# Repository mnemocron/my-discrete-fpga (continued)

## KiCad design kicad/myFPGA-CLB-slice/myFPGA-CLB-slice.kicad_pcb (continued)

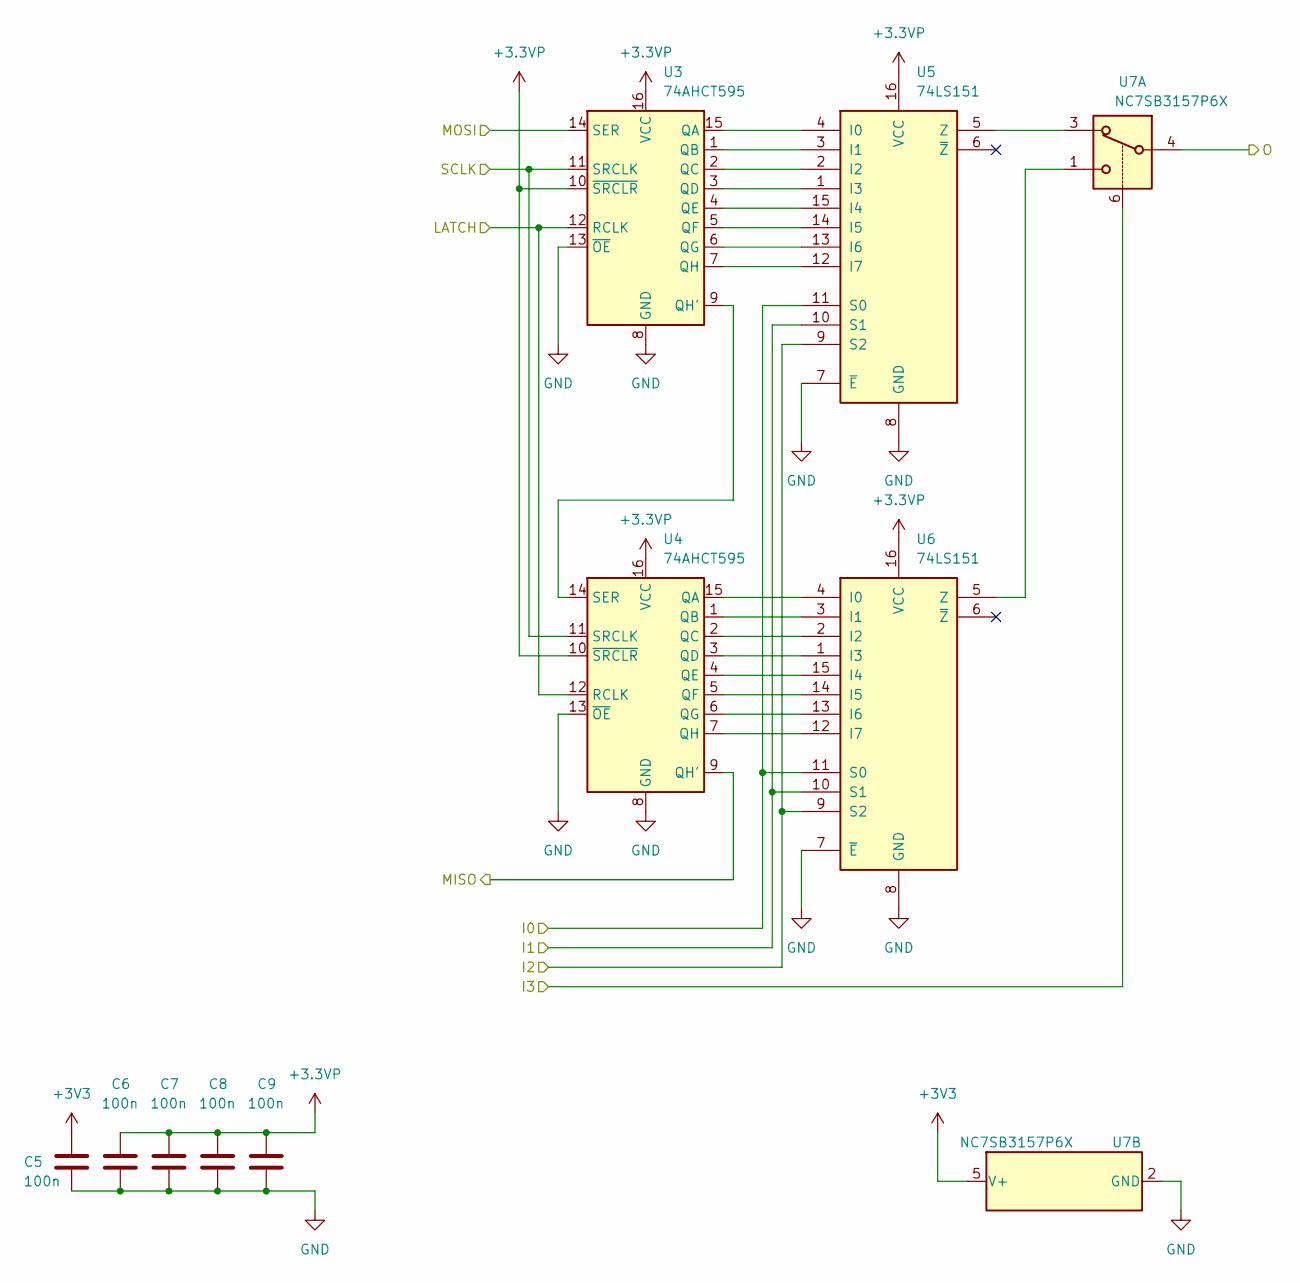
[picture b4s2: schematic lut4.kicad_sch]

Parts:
C5, C6, C7, C8, C9: 100n; C_0603_1608Metric; Voltage 50; Part Nr. CC0603KRX7R9BB104; JLCPCB Part # C14663
U3, U4: 74AHCT595; SOIC-16_3.9x9.9mm_P1.27mm; Part Nr. 74HC595D; JLCPCB Part # C5947
U5, U6: 74LS151; TSSOP-16_4.4x5mm_P0.65mm; Part Nr. MC74HC151ADTR2G; JLCPCB Part # C152523
U7: NC7SB3157P6X; SOT-363_SC-70-6; Part Nr. 74LVC1G157GW; JLCPCB Part # C135822

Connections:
+3.3VP: C6.1, C7.1, C8.1, C9.1, U3.10 (~SRCLR), U3.16 (VCC), U4.10 (~SRCLR), U4.16 (VCC), U5.16 (VCC), U6.16 (VCC); also elsewhere on the board
+3V3: C5.1, U7.5 (V+); also elsewhere on the board
/CBpre_2: U5.9 (S2), U6.9 (S2); also elsewhere on the board
/CBpre_3: U7.6; also elsewhere on the board
/D0: U5.10 (S1), U6.10 (S1); also elsewhere on the board
/D1: U5.11 (S0), U6.11 (S0); also elsewhere on the board
/Input Selector/MISO: U3.14 (SER); also elsewhere on the board
/LUT4_0/MISO: U4.9 (QH'); also elsewhere on the board
/Ld: U7.4; also elsewhere on the board
GND: C5.2, C6.2, C7.2, C8.2, C9.2, U3.8 (GND), U3.13 (~OE), U4.8 (GND), U4.13 (~OE), U5.7 (~E), U5.8 (GND), U6.7 (~E), U6.8 (GND), U7.2 (GND); also elsewhere on the board
LATCH: U3.12 (RCLK), U4.12 (RCLK); also elsewhere on the board
unnamed: U3.15 (QA), U5.4 (I0)
unnamed: U3.1 (QB), U5.3 (I1)
unnamed: U3.2 (QC), U5.2 (I2)
unnamed: U3.3 (QD), U5.1 (I3)
unnamed: U3.4 (QE), U5.15 (I4)
unnamed: U3.5 (QF), U5.14 (I5)
unnamed: U3.6 (QG), U5.13 (I6)
unnamed: U3.9 (QH'), U4.14 (SER)
unnamed: U3.7 (QH), U5.12 (I7)
unnamed: U4.15 (QA), U6.4 (I0)
unnamed: U4.1 (QB), U6.3 (I1)
unnamed: U4.2 (QC), U6.2 (I2)
unnamed: U4.3 (QD), U6.1 (I3)
unnamed: U4.4 (QE), U6.15 (I4)
unnamed: U4.5 (QF), U6.14 (I5)
unnamed: U4.6 (QG), U6.13 (I6)
unnamed: U4.7 (QH), U6.12 (I7)
unnamed: U5.5 (Z), U7.3
unnamed: U6.5 (Z), U7.1
SCLK: U3.11 (SRCLK), U4.11 (SRCLK); also elsewhere on the board

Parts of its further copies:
C20, C21, C22, C23, C24, C25, C26, C27, C28, C29, C30, C31, C32, C33, C34: 100n; C_0603_1608Metric; Voltage 50; Part Nr. CC0603KRX7R9BB104; JLCPCB Part # C14663
U19, U20, U24, U25, U29, U30: 74AHCT595; SOIC-16_3.9x9.9mm_P1.27mm; Part Nr. 74HC595D; JLCPCB Part # C5947
U21, U22, U26, U27, U31, U32: 74LS151; TSSOP-16_4.4x5mm_P0.65mm; Part Nr. MC74HC151ADTR2G; JLCPCB Part # C152523
U23, U28, U33: NC7SB3157P6X; SOT-363_SC-70-6; Part Nr. 74LVC1G157GW; JLCPCB Part # C135822

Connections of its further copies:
+3.3VP: C21.1, C22.1, C23.1, C24.1, C26.1, C27.1, C28.1, C29.1, C31.1, C32.1, C33.1, C34.1, U19.10 (~SRCLR), U19.16 (VCC), U20.10 (~SRCLR), U20.16 (VCC), U21.16 (VCC), U22.16 (VCC), U24.10 (~SRCLR), U24.16 (VCC), U25.10 (~SRCLR), U25.16 (VCC), U26.16 (VCC), U27.16 (VCC), U29.10 (~SRCLR), U29.16 (VCC), U30.10 (~SRCLR), U30.16 (VCC), U31.16 (VCC), U32.16 (VCC); also elsewhere on the board
+3V3: C20.1, C25.1, C30.1, U23.5 (V+), U28.5 (V+), U33.5 (V+); also elsewhere on the board
/A0: U31.10 (S1), U32.10 (S1); also elsewhere on the board
/A1: U31.11 (S0), U32.11 (S0); also elsewhere on the board
/B0: U26.10 (S1), U27.10 (S1); also elsewhere on the board
/B1: U26.11 (S0), U27.11 (S0); also elsewhere on the board
/C0: U21.10 (S1), U22.10 (S1); also elsewhere on the board
/C1: U21.11 (S0), U22.11 (S0); also elsewhere on the board
/CBpre_2: U21.9 (S2), U22.9 (S2), U26.9 (S2), U27.9 (S2), U31.9 (S2), U32.9 (S2); also elsewhere on the board
/CBpre_3: U23.6, U28.6, U33.6; also elsewhere on the board
/LUT4_0/MISO: U19.14 (SER); also elsewhere on the board
/LUT4_1/MISO: U20.9 (QH'), U24.14 (SER)
/LUT4_2/MISO: U25.9 (QH'), U29.14 (SER)
/LUT4_3/MISO: U30.9 (QH'); also elsewhere on the board
/La: U33.4; also elsewhere on the board
/Lb: U28.4; also elsewhere on the board
/Lc: U23.4; also elsewhere on the board
GND: C20.2, C21.2, C22.2, C23.2, C24.2, C25.2, C26.2, C27.2, C28.2, C29.2, C30.2, C31.2, C32.2, C33.2, C34.2, U19.8 (GND), U19.13 (~OE), U20.8 (GND), U20.13 (~OE), U21.7 (~E), U21.8 (GND), U22.7 (~E), U22.8 (GND), U23.2 (GND), U24.8 (GND), U24.13 (~OE), U25.8 (GND), U25.13 (~OE), U26.7 (~E), U26.8 (GND), U27.7 (~E), U27.8 (GND), U28.2 (GND), U29.8 (GND), U29.13 (~OE), U30.8 (GND), U30.13 (~OE), U31.7 (~E), U31.8 (GND), U32.7 (~E), U32.8 (GND), U33.2 (GND); also elsewhere on the board
LATCH: U19.12 (RCLK), U20.12 (RCLK), U24.12 (RCLK), U25.12 (RCLK), U29.12 (RCLK), U30.12 (RCLK); also elsewhere on the board
unnamed: U19.15 (QA), U21.4 (I0)
unnamed: U19.1 (QB), U21.3 (I1)
unnamed: U19.2 (QC), U21.2 (I2)
unnamed: U19.3 (QD), U21.1 (I3)
unnamed: U19.4 (QE), U21.15 (I4)
unnamed: U19.5 (QF), U21.14 (I5)
unnamed: U19.6 (QG), U21.13 (I6)
unnamed: U19.9 (QH'), U20.14 (SER)
unnamed: U19.7 (QH), U21.12 (I7)
unnamed: U20.15 (QA), U22.4 (I0)
unnamed: U20.1 (QB), U22.3 (I1)
unnamed: U20.2 (QC), U22.2 (I2)
unnamed: U20.3 (QD), U22.1 (I3)
unnamed: U20.4 (QE), U22.15 (I4)
unnamed: U20.5 (QF), U22.14 (I5)
unnamed: U20.6 (QG), U22.13 (I6)
unnamed: U20.7 (QH), U22.12 (I7)
unnamed: U21.5 (Z), U23.3
unnamed: U22.5 (Z), U23.1
unnamed: U24.15 (QA), U26.4 (I0)
unnamed: U24.1 (QB), U26.3 (I1)
unnamed: U24.2 (QC), U26.2 (I2)
unnamed: U24.3 (QD), U26.1 (I3)
unnamed: U24.4 (QE), U26.15 (I4)
unnamed: U24.5 (QF), U26.14 (I5)
unnamed: U24.6 (QG), U26.13 (I6)
unnamed: U24.9 (QH'), U25.14 (SER)
unnamed: U24.7 (QH), U26.12 (I7)
unnamed: U25.15 (QA), U27.4 (I0)
unnamed: U25.1 (QB), U27.3 (I1)
unnamed: U25.2 (QC), U27.2 (I2)
unnamed: U25.3 (QD), U27.1 (I3)
unnamed: U25.4 (QE), U27.15 (I4)
unnamed: U25.5 (QF), U27.14 (I5)
unnamed: U25.6 (QG), U27.13 (I6)
unnamed: U25.7 (QH), U27.12 (I7)
unnamed: U26.5 (Z), U28.3
unnamed: U27.5 (Z), U28.1
unnamed: U29.15 (QA), U31.4 (I0)
unnamed: U29.1 (QB), U31.3 (I1)
unnamed: U29.2 (QC), U31.2 (I2)
unnamed: U29.3 (QD), U31.1 (I3)
unnamed: U29.4 (QE), U31.15 (I4)
unnamed: U29.5 (QF), U31.14 (I5)
unnamed: U29.6 (QG), U31.13 (I6)
unnamed: U29.9 (QH'), U30.14 (SER)
unnamed: U29.7 (QH), U31.12 (I7)
unnamed: U30.15 (QA), U32.4 (I0)
unnamed: U30.1 (QB), U32.3 (I1)
unnamed: U30.2 (QC), U32.2 (I2)
unnamed: U30.3 (QD), U32.1 (I3)
unnamed: U30.4 (QE), U32.15 (I4)
unnamed: U30.5 (QF), U32.14 (I5)
unnamed: U30.6 (QG), U32.13 (I6)
unnamed: U30.7 (QH), U32.12 (I7)
unnamed: U31.5 (Z), U33.3
unnamed: U32.5 (Z), U33.1
SCLK: U19.11 (SRCLK), U20.11 (SRCLK), U24.11 (SRCLK), U25.11 (SRCLK), U29.11 (SRCLK), U30.11 (SRCLK); also elsewhere on the board

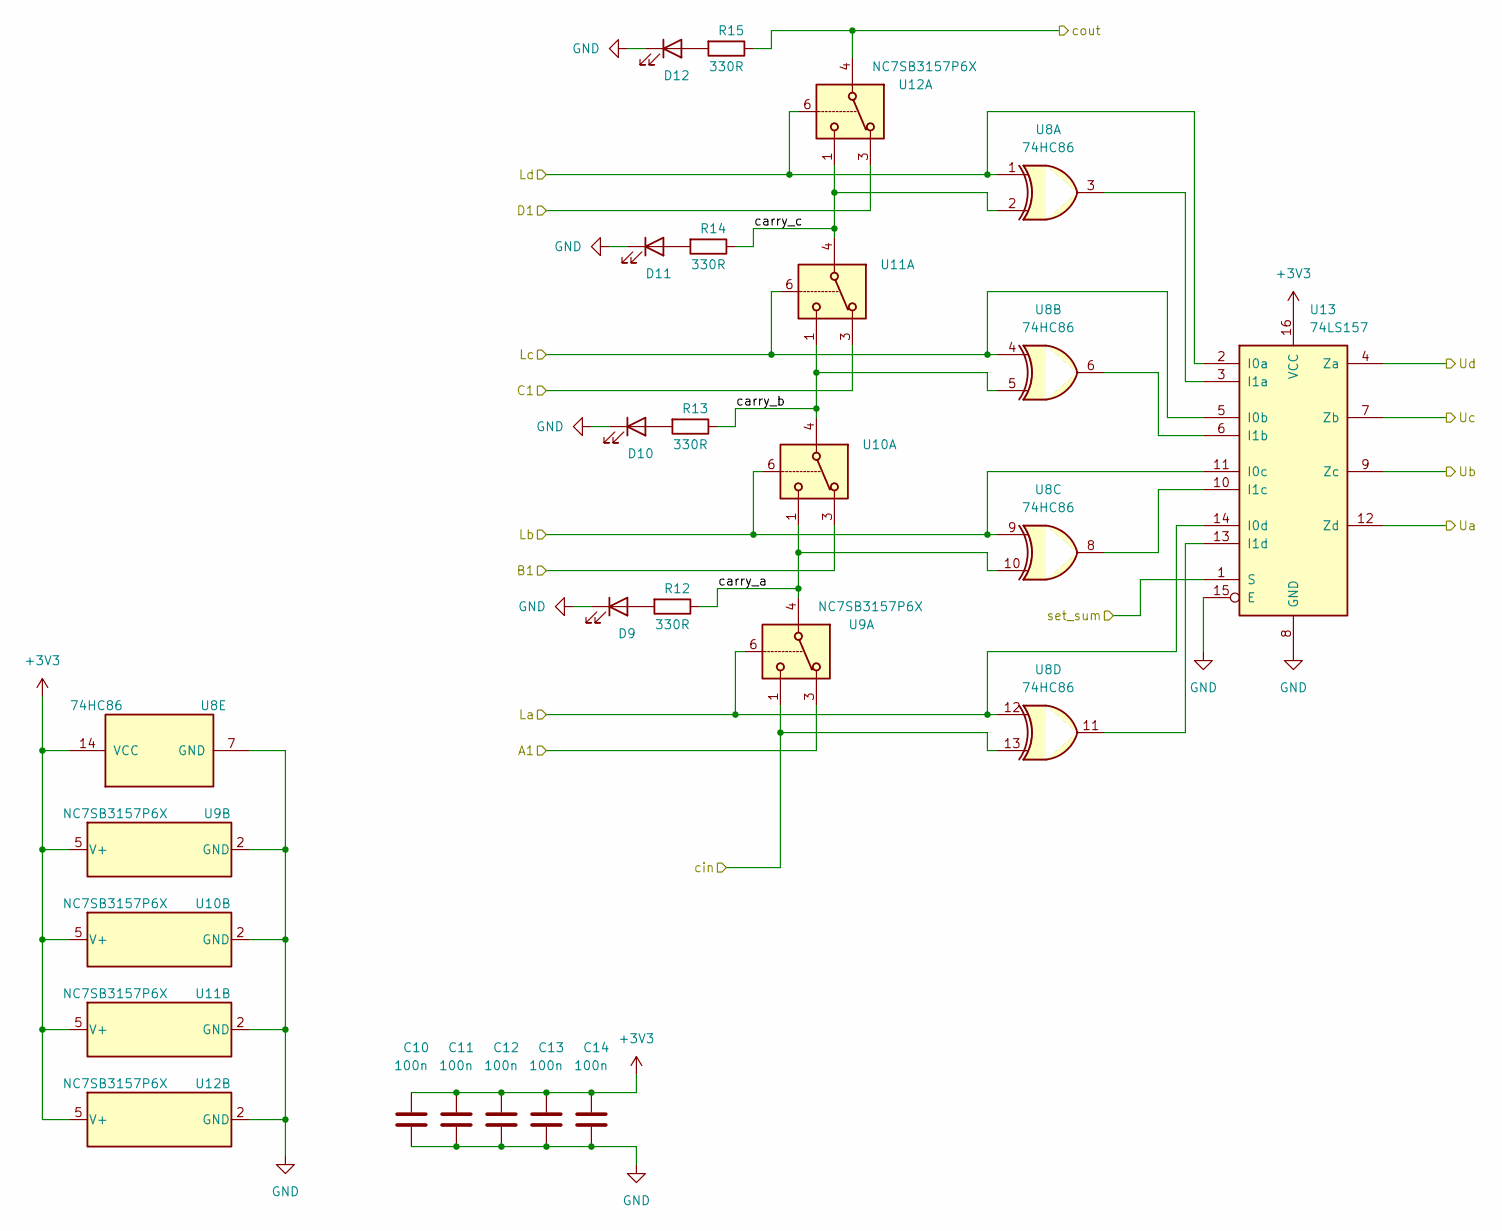
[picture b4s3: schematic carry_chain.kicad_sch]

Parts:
C10, C11, C12, C13, C14: 100n; C_0603_1608Metric; Voltage 50; Part Nr. CC0603KRX7R9BB104; JLCPCB Part # C14663
D9, D10, D11, D12: LED (blue); LED_0603_1608Metric; Part Nr. 19-217/BHC-ZL1M2RY/3T; JLCPCB Part # C72041
R12, R13, R14, R15: 330R; R_0603_1608Metric; Part Nr. 0603WAF3300T5E; JLCPCB Part # C23138
U8: 74HC86; SOIC-14_3.9x8.7mm_P1.27mm; Part Nr. SN74AHC86DR; JLCPCB Part # C8175
U9, U10, U11, U12: NC7SB3157P6X; SOT-363_SC-70-6; Part Nr. 74LVC1G157GW; JLCPCB Part # C135822
U13: 74LS157; SOIC-16_3.9x9.9mm_P1.27mm; Part Nr. SN74HC157DR; JLCPCB Part # C6823

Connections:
+3V3: C10.1, C11.1, C12.1, C13.1, C14.1, U8.14 (VCC), U9.5 (V+), U10.5 (V+), U11.5 (V+), U12.5 (V+), U13.16 (VCC); also elsewhere on the board
/A0: U9.3; also elsewhere on the board
/B0: U10.3; also elsewhere on the board
/C0: U11.3; also elsewhere on the board
/Carry Chain/carry_a: R12.1, U8.10, U9.4, U10.1
/Carry Chain/carry_b: R13.1, U8.5, U10.4, U11.1
/Carry Chain/carry_c: R14.1, U8.2, U11.4, U12.1
/D0: U12.3; also elsewhere on the board
/La: U8.12, U9.6, U13.14 (I0d); also elsewhere on the board
/Lb: U8.9, U10.6, U13.11 (I0c); also elsewhere on the board
/Lc: U8.4, U11.6, U13.5 (I0b); also elsewhere on the board
/Ld: U8.1, U12.6, U13.2 (I0a); also elsewhere on the board
/Oa: U13.12 (Zd); also elsewhere on the board
/Ob: U13.9 (Zc); also elsewhere on the board
/Oc: U13.7 (Zb); also elsewhere on the board
/Od: U13.4 (Za); also elsewhere on the board
/cin: U8.13, U9.1; also elsewhere on the board
/cout: R15.1, U12.4; also elsewhere on the board
GND: C10.2, C11.2, C12.2, C13.2, C14.2, D9.1 (K), D10.1 (K), D11.1 (K), D12.1 (K), U8.7 (GND), U9.2 (GND), U10.2 (GND), U11.2 (GND), U12.2 (GND), U13.8 (GND), U13.15 (E); also elsewhere on the board
unnamed: D9.2 (A), R12.2
unnamed: D10.2 (A), R13.2
unnamed: D11.2 (A), R14.2
unnamed: D12.2 (A), R15.2
unnamed: U8.3, U13.3 (I1a)
unnamed: U8.6, U13.6 (I1b)
unnamed: U8.8, U13.10 (I1c)
unnamed: U8.11, U13.13 (I1d)
set_sum: U13.1 (S); also elsewhere on the board

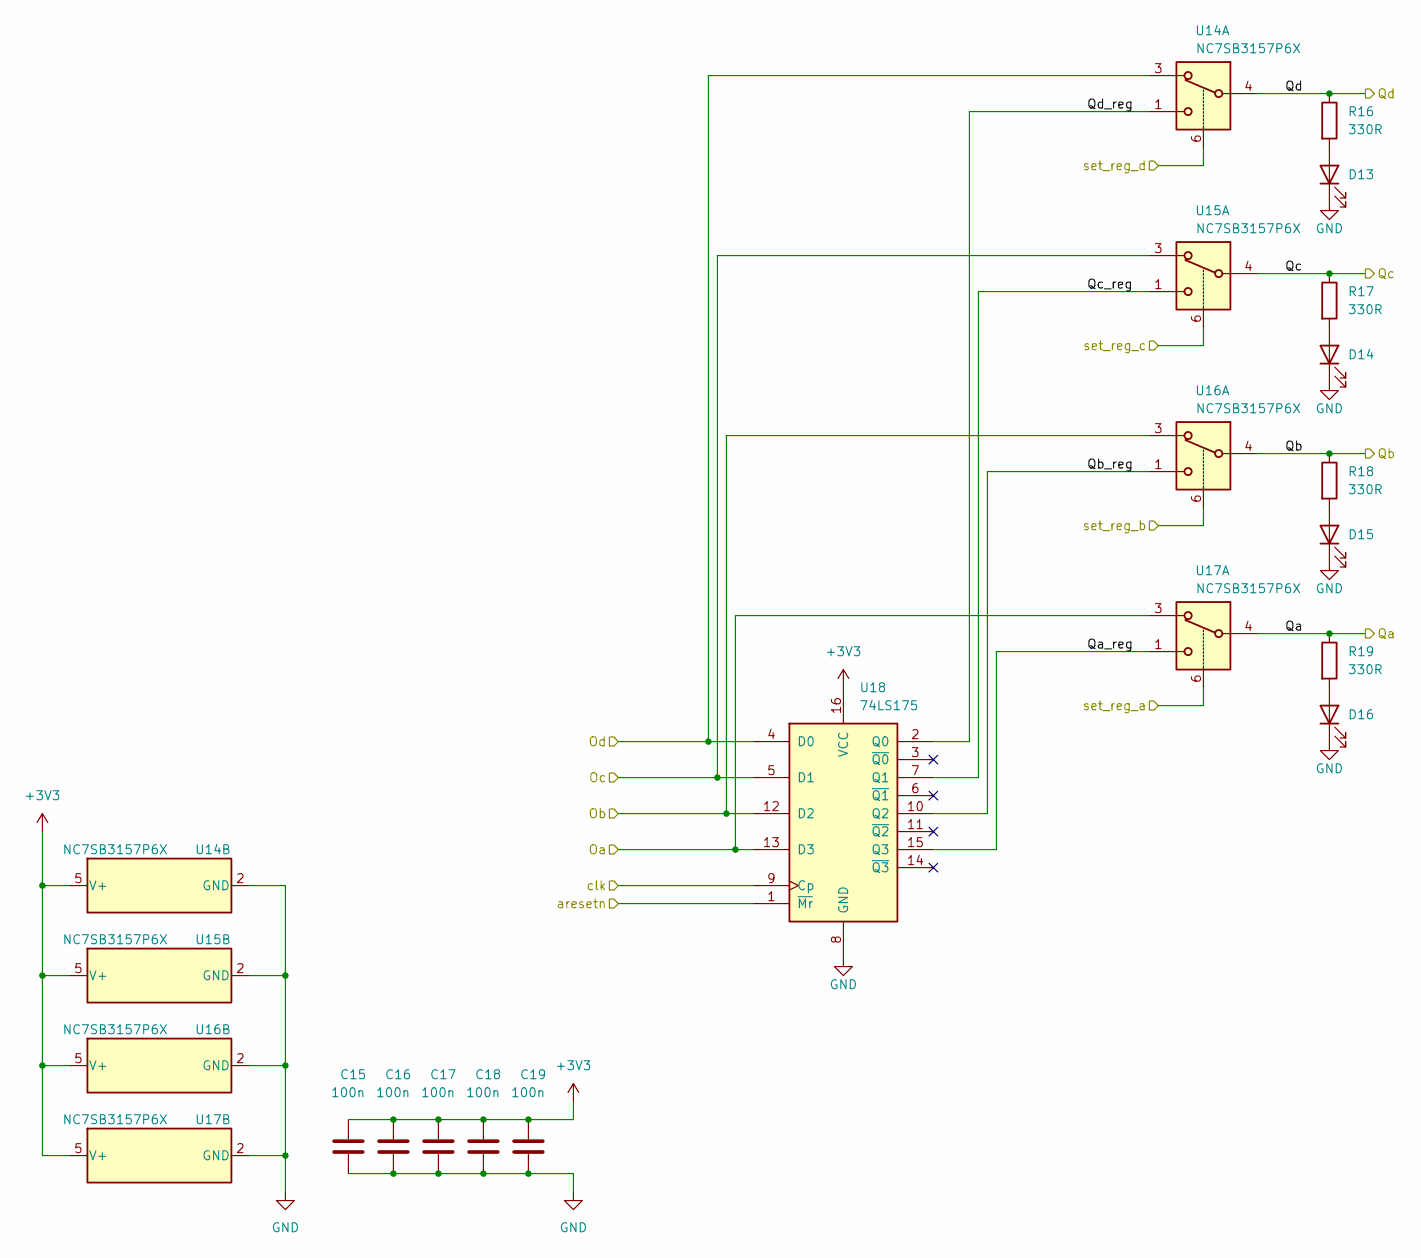
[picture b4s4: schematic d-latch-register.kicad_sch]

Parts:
C15, C16, C17, C18, C19: 100n; C_0603_1608Metric; Voltage 50; Part Nr. CC0603KRX7R9BB104; JLCPCB Part # C14663
D13, D14, D15, D16: LED (blue); LED_0603_1608Metric; Part Nr. 19-217/BHC-ZL1M2RY/3T; JLCPCB Part # C72041
R16, R17, R18, R19: 330R; R_0603_1608Metric; Part Nr. 0603WAF3300T5E; JLCPCB Part # C23138
U14, U15, U16, U17: NC7SB3157P6X; SOT-363_SC-70-6; Part Nr. 74LVC1G157GW; JLCPCB Part # C135822
U18: 74LS175; SOIC-16_3.9x9.9mm_P1.27mm; Part Nr. CD74AC175M96; JLCPCB Part # C8180

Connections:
+3V3: C15.1, C16.1, C17.1, C18.1, C19.1, U14.5 (V+), U15.5 (V+), U16.5 (V+), U17.5 (V+), U18.16 (VCC); also elsewhere on the board
/D-Latch/Qa: R19.1, U17.4; also elsewhere on the board
/D-Latch/Qa_reg: U17.1, U18.15 (Q3)
/D-Latch/Qb: R18.1, U16.4; also elsewhere on the board
/D-Latch/Qb_reg: U16.1, U18.10 (Q2)
/D-Latch/Qc: R17.1, U15.4; also elsewhere on the board
/D-Latch/Qc_reg: U15.1, U18.7 (Q1)
/D-Latch/Qd: R16.1, U14.4; also elsewhere on the board
/D-Latch/Qd_reg: U14.1, U18.2 (Q0)
/Oa: U17.3, U18.13 (D3); also elsewhere on the board
/Ob: U16.3, U18.12 (D2); also elsewhere on the board
/Oc: U15.3, U18.5 (D1); also elsewhere on the board
/Od: U14.3, U18.4 (D0); also elsewhere on the board
GND: C15.2, C16.2, C17.2, C18.2, C19.2, D13.1 (K), D14.1 (K), D15.1 (K), D16.1 (K), U14.2 (GND), U15.2 (GND), U16.2 (GND), U17.2 (GND), U18.8 (GND); also elsewhere on the board
unnamed: D13.2 (A), R16.2
unnamed: D14.2 (A), R17.2
unnamed: D15.2 (A), R18.2
unnamed: D16.2 (A), R19.2
aresetn: U18.1 (~Mr); also elsewhere on the board
latch_clk: U18.9 (Cp); also elsewhere on the board
set_reg_a: U17.6; also elsewhere on the board
set_reg_b: U16.6; also elsewhere on the board
set_reg_c: U15.6; also elsewhere on the board
set_reg_d: U14.6; also elsewhere on the board

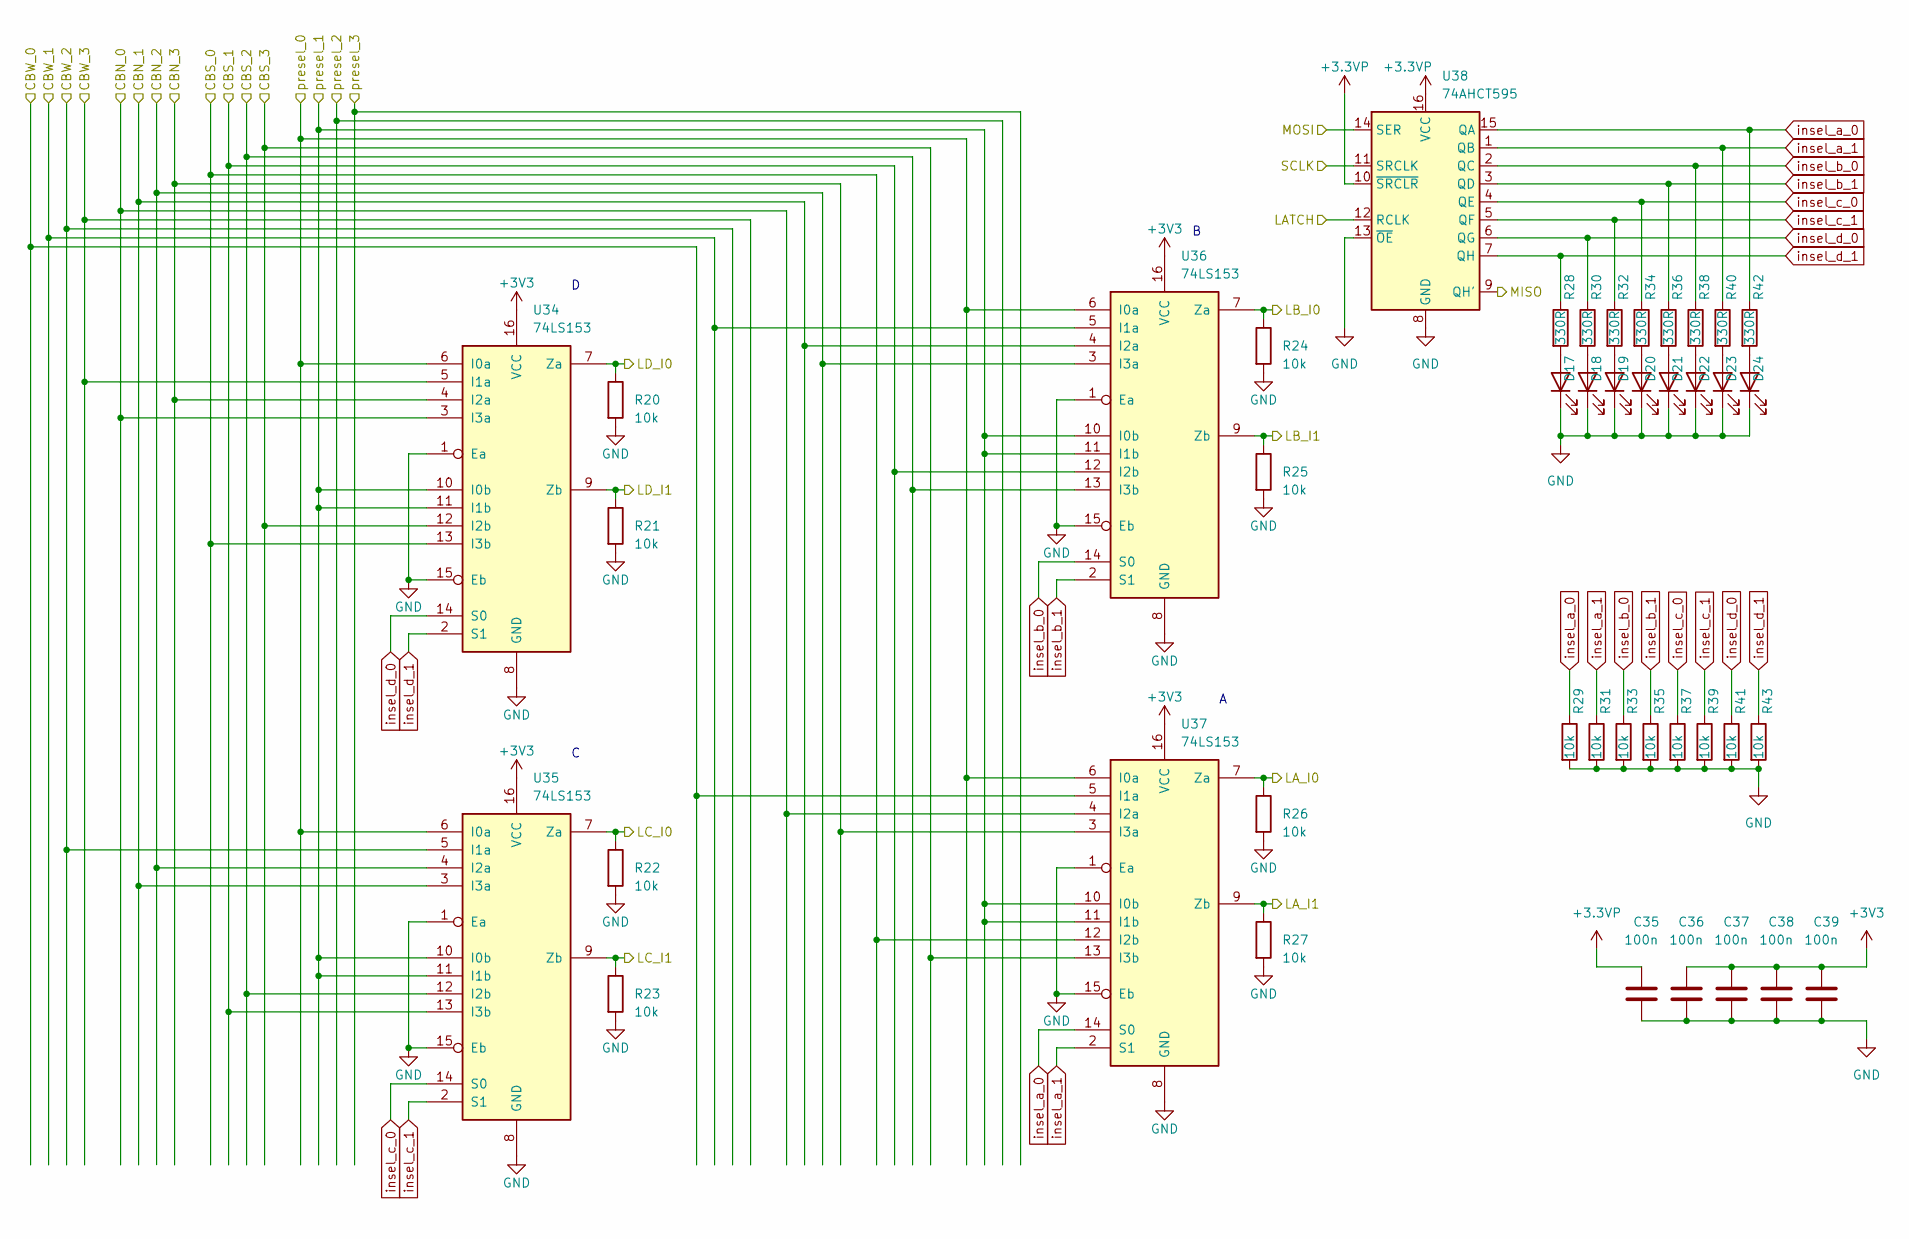
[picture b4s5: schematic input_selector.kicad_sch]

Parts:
C35, C36, C37, C38, C39: 100n; C_0603_1608Metric; Voltage 50; Part Nr. CC0603KRX7R9BB104; JLCPCB Part # C14663
D17, D18, D19, D20, D21, D22, D23, D24: LED (green); LED_0805_2012Metric; Part Nr. C2297; JLCPCB Part # C2297
R20, R21, R22, R23, R24, R25, R26, R27, R29, R31, R33, R35, R37, R39, R41, R43: 10k; R_0603_1608Metric; Part Nr. 0603WAF1002T5E; JLCPCB Part # C25804
R28, R30, R32, R34, R36, R38, R40, R42: 330R; R_0603_1608Metric; Part Nr. 0603WAF3300T5E; JLCPCB Part # C23138
U34, U35, U36, U37: 74LS153; TSSOP-16_4.4x5mm_P0.65mm; Part Nr. 74HC153D; JLCPCB Part # C150159
U38: 74AHCT595; SOIC-16_3.9x9.9mm_P1.27mm; Part Nr. 74HC595D; JLCPCB Part # C5947

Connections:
+3.3VP: C35.1, U38.10 (~SRCLR), U38.16 (VCC); also elsewhere on the board
+3V3: C36.1, C37.1, C38.1, C39.1, U34.16 (VCC), U35.16 (VCC), U36.16 (VCC), U37.16 (VCC); also elsewhere on the board
/A0: R26.1, U37.7 (Za); also elsewhere on the board
/A1: R27.1, U37.9 (Zb); also elsewhere on the board
/B0: R24.1, U36.7 (Za); also elsewhere on the board
/B1: R25.1, U36.9 (Zb); also elsewhere on the board
/C0: R22.1, U35.7 (Za); also elsewhere on the board
/C1: R23.1, U35.9 (Zb); also elsewhere on the board
/CBpre_0: U34.6 (I0a), U35.6 (I0a), U36.6 (I0a), U37.6 (I0a); also elsewhere on the board
/CBpre_1: U34.10 (I0b), U34.11 (I1b), U35.10 (I0b), U35.11 (I1b), U36.10 (I0b), U36.11 (I1b), U37.10 (I0b), U37.11 (I1b); also elsewhere on the board
/CBw_0: U37.5 (I1a); also elsewhere on the board
/CBw_1: U36.5 (I1a); also elsewhere on the board
/CBw_2: U35.5 (I1a); also elsewhere on the board
/CBw_3: U34.5 (I1a); also elsewhere on the board
/D0: R20.1, U34.7 (Za); also elsewhere on the board
/D1: R21.1, U34.9 (Zb); also elsewhere on the board
/Input Selector/CBN_0: U34.3 (I3a), U37.4 (I2a); also elsewhere on the board
/Input Selector/CBN_1: U35.3 (I3a), U36.4 (I2a); also elsewhere on the board
/Input Selector/CBN_2: U35.4 (I2a), U36.3 (I3a); also elsewhere on the board
/Input Selector/CBN_3: U34.4 (I2a), U37.3 (I3a); also elsewhere on the board
/Input Selector/CBS_0: U34.13 (I3b), U37.12 (I2b); also elsewhere on the board
/Input Selector/CBS_1: U35.13 (I3b), U36.12 (I2b); also elsewhere on the board
/Input Selector/CBS_2: U35.12 (I2b), U36.13 (I3b); also elsewhere on the board
/Input Selector/CBS_3: U34.12 (I2b), U37.13 (I3b); also elsewhere on the board
/Input Selector/MISO: U38.9 (QH'); also elsewhere on the board
GND: C35.2, C36.2, C37.2, C38.2, C39.2, D17.1 (K), D18.1 (K), D19.1 (K), D20.1 (K), D21.1 (K), D22.1 (K), D23.1 (K), D24.1 (K), R20.2, R21.2, R22.2, R23.2, R24.2, R25.2, R26.2, R27.2, R29.2, R31.2, R33.2, R35.2, R37.2, R39.2, R41.2, R43.2, U34.1 (Ea), U34.8 (GND), U34.15 (Eb), U35.1 (Ea), U35.8 (GND), U35.15 (Eb), U36.1 (Ea), U36.8 (GND), U36.15 (Eb), U37.1 (Ea), U37.8 (GND), U37.15 (Eb), U38.8 (GND), U38.13 (~OE); also elsewhere on the board
LATCH: U38.12 (RCLK); also elsewhere on the board
MOSI: U38.14 (SER); also elsewhere on the board
unnamed: D17.2 (A), R28.2
unnamed: D18.2 (A), R30.2
unnamed: D19.2 (A), R32.2
unnamed: D20.2 (A), R34.2
unnamed: D21.2 (A), R36.2
unnamed: D22.2 (A), R38.2
unnamed: D23.2 (A), R40.2
unnamed: D24.2 (A), R42.2
SCLK: U38.11 (SRCLK); also elsewhere on the board
insel_a_0: R29.1, R42.1, U37.14 (S0), U38.15 (QA)
insel_a_1: R31.1, R40.1, U37.2 (S1), U38.1 (QB)
insel_b_0: R33.1, R38.1, U36.14 (S0), U38.2 (QC)
insel_b_1: R35.1, R36.1, U36.2 (S1), U38.3 (QD)
insel_c_0: R34.1, R37.1, U35.14 (S0), U38.4 (QE)
insel_c_1: R32.1, R39.1, U35.2 (S1), U38.5 (QF)
insel_d_0: R30.1, R41.1, U34.14 (S0), U38.6 (QG)
insel_d_1: R28.1, R43.1, U34.2 (S1), U38.7 (QH)

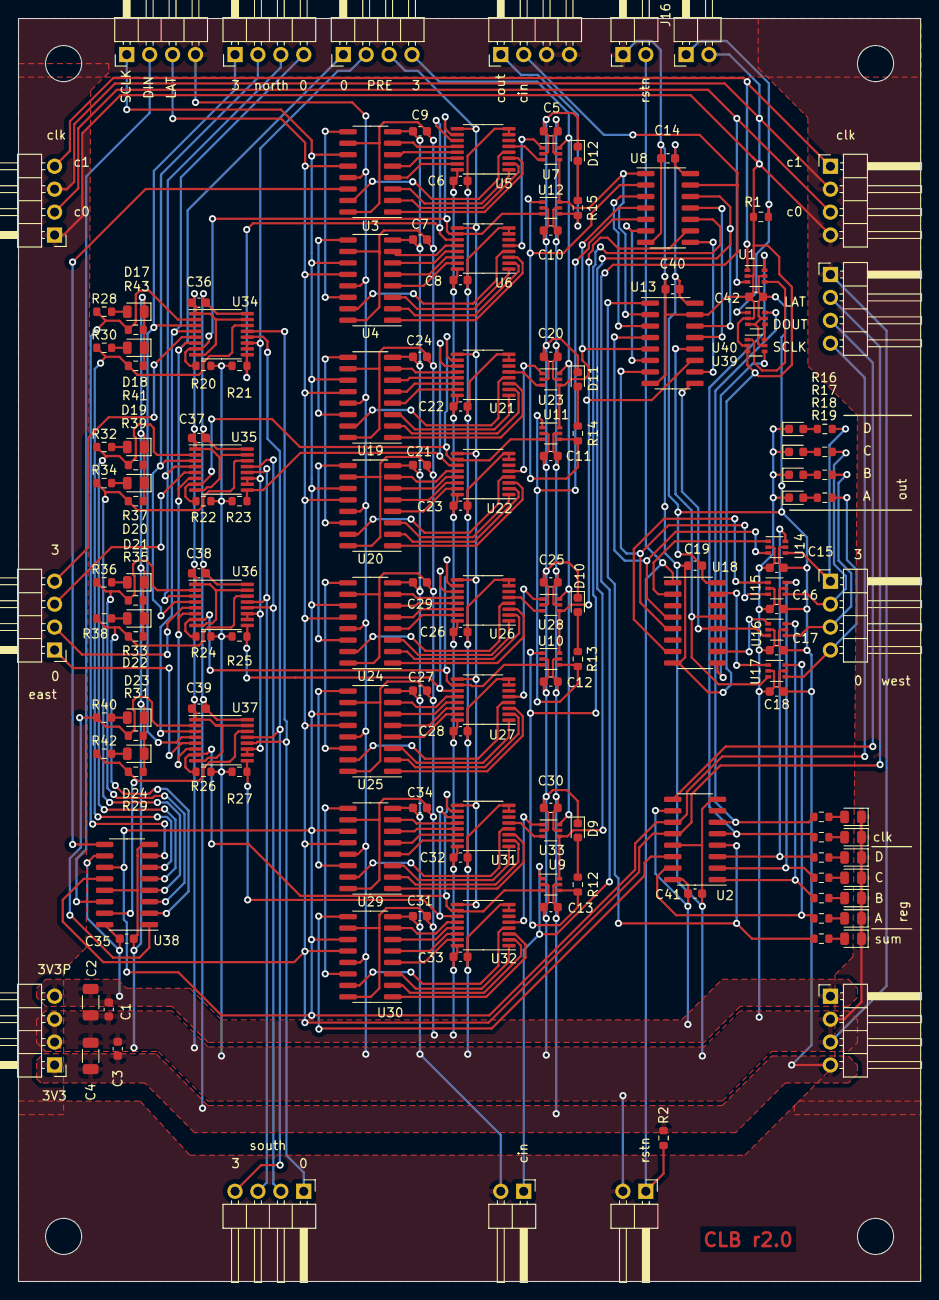
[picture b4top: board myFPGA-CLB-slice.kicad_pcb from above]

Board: 2 copper layers, 100.0 x 140.0 mm, 162 parts (0 on the bottom side), 182 nets.

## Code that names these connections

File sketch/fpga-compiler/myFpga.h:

#include <Arduino.h>

#ifndef MY_FPGA_H
#define	MY_FPGA_H

#define N_BYTES_CLB (10)
#define N_BYTES_CBV (1)
#define N_BYTES_CBH (2)
#define N_BYTES_CSW (4)
#define N_BYTES_SLICE (N_BYTES_CLB + N_BYTES_CBV + N_BYTES_CBH + N_BYTES_CSW)

#define N_SLICE_X (1)
#define N_SLICE_Y (1)

#define ENABLE_PRINT_MESSAGES true

typedef enum {
  GND = 0,
  VCC = 1,
  BUS_5 = 2,
  BUS_4 = 3,
  BUS_3 = 4,
  BUS_2 = 5,
  BUS_1 = 6,
  BUS_0 = 7
} cbh_select_t;

typedef struct {
  cbh_select_t sel[4];
  bool ce;
  bool cin;
  bool cout_n;
  bool cout_s;
} cbh_t;

typedef struct {
  bool bus[4];
  bool bus_0_to_5;
  bool bus_2_to_5;
  bool bus_1_to_4;
  bool bus_3_to_4;
} cbv_t;

typedef struct {
  bool north[6];
  bool south[6];
  bool east[6];
  bool west[6];
  bool xp[6];
  bool ns4_to_ew5;
  bool ns5_to_ew4;
} sw_t;

typedef enum {
  PRE = 0,
  LUT_EXPAND = 1,
  SUM_INPUT = 2,
  SUM_INPUT_REVERSED = 3
} insel_t;

typedef struct {
  bool reg[4];
  bool sum;
  int clk_sel;
  bool clk_en;
  uint16_t lut[4];
  insel_t in_mux[4];
} clb_t;

typedef struct {
  int pos_x;
  int pos_y;
  clb_t clb;
  cbv_t cbv;
  cbh_t cbh;
  sw_t  sw;
  char bitstream[N_BYTES_SLICE];
} slice_t;

typedef struct {
  slice_t slice[N_SLICE_X][N_SLICE_Y];
  int Nx;
  int Ny;
} fpga_t;

int create_bitstream(fpga_t* fpga);

#endif	/* MY_FPGA_H */

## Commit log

2023-09-04 added GHDL/cocotb gitignore
2023-09-04 added kicad to gitignore
2023-09-04 added VHDL code of 7400 multiplexers
2023-09-04 VHDL sim of CLB slice successful\nrequires assert statements\nsum and carry chain not yet tested
2023-09-04 debugging sum mode in CLB
2023-09-04 added latex to gitignore
2023-09-04 added drawio to gitignore
2023-09-04 added doc
2023-09-04 added kicad CLB (wip)
2023-09-05 CLB working but verification not
2023-09-05 CLB verification fixed
2023-09-05 fixed CLB arch graphic
2023-09-05 fixed kicad names, updated architecure, started CBv
2023-09-06 found a way to model the connection box
2023-09-06 changed all std_Ulogic to std_logic
2023-09-06 kicad -> pcb started
2023-09-06 CBh model complete, requires self checking TB
2023-09-07 new crosspoint helper IP, started Switchbox
2023-09-07 kicad: picked JLC parts, fixed routing to match VHDL, started layouting
2023-09-09 added python to gitignore
2023-09-09 added simple Lexer for iHDL
2023-09-10 started markdown doc
2023-09-12 CLB doc in md
2023-10-28 update 74LS175 to arstn in vhdl
2023-10-28 update 74LS175 in CLB simulation
2023-10-28 restart PCB layout
2023-10-28 new testbench concept
2023-10-28 i frogot
2023-10-28 increas cb_west from 2 to 4 ports
2023-10-28 added toggle_bit test case for entire slice\nfound some bugs with bitstream order
2023-10-28 fixed some bugs in the architecture documentation
2023-10-29 potentially unsolvable bug with xpoint simulation
2023-10-29 progress in pcb of CLB
2023-10-30 2 layer pcb for clb seems complete (awaits review)
2023-10-31 new approach to transistor level simulation for xpoint switch seems to work
2023-10-31 new xpoint switch seems to work
2023-10-31 new bitstream documentation (LUT fields are wrong)
2023-11-02 start of new md documentation
2023-11-02 add ihdl concept
2023-11-02 several bugs in bitstream occurred - configuration bits in VHDL model do not match with PCB - configuration bits in VHDL don't match with excel sheet - set_reg_* bits don't map correctly - LUT bits d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
    let's just redo the entire bitstream documentation.
    take PCB as reference, adapt to VHDL, document in excel
2023-11-05 IT WORKS! first successful bit toggle simulation using all 4 tile elements - fixed bitstream order issue - fixed delta loop problem - simulation is ready for bitstreams
2023-11-05 fixed a footprint
2023-11-06 fixed a footprint, changed to 2 Layer stackup
2023-12-04 add kicad gerber outputs to gitignore
2023-12-04 gitignore fix
2023-12-28 generate new images
2023-12-28 experiment with assembled PCB
2024-01-02 started kicad projects for interconnect
2024-01-02 update bitstream documentation
2024-01-02 start layout of SW box
2024-01-03 SWbox layout nearly complete
2024-01-04 verified matching bitstream between PCB and VHDL
2024-01-06 sw box layout almost complete
2024-01-08 more compiler work
2024-01-08 more kicad layouts
2024-01-10 more kicad layouts 2.
2024-01-15 CLB requires rev.2
2024-01-17 CLB slice rev. 2.0 - fix aresetn pullup instead of pulldown - new feature: clock enable - fixes S0 and S1 flipped
2024-01-18 start new feature CE
2024-02-13 GPIO concept
2024-02-13 PCB renders
2024-02-20 found more bugs
2024-02-20 rm files
2024-02-21 first working tests on a full hardware slice
2024-02-25 fix wrong bitstream order
2024-03-04 updated VHDL model to match PCB
2024-03-04 update?
2024-03-04 include CE in CLB
2024-03-08 fixed CE throughout simulation
2024-03-08 update README before pulishing
2024-03-14 refactor VHDL to remove "prio" bus and merge into regular bus(5 downto 0)
2024-03-14 remove final occurrences of the word "prio"
2024-03-16 cleanup architecture
2024-03-17 cleanup repository
2024-03-17 unfinished test: 4-bit counter
2024-04-13 built a working "compiler" in C for Arduino
2024-04-14 bitstream compiler WIP
2024-04-14 working compiler :)
2024-04-14 fix bugs in compiler, add another slice -> working :D
2024-04-17 updated images for blogpost
2024-04-20 ready for first release - fixed Arduino compiler - more documentation - tested SUM mode on 3 Tiles (physical PCB)
